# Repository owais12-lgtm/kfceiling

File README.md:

# kfceiling

# About
This is a macropad that has 8 programmable kets with a oled display and encoder! 

# Images

" height="626" alt="image" src="https://github.com/user-attachments/assets/a1786a0a-3907-4cc6-ba57-133aeb5b290b" />

# BOM

| Name | Purpose | Quantity | Total Cost (USD) | Link | Distributor |
|---|---|---|---|---|---|
| pcb | pcb | 1 | $0.00 | [robu.in](https://robu.in/product/online-pcb-manufacturing-service/) | robu |
| nice nano | mcu | 1 | $9.00 | [robu.in](https://robu.in/product/promicro-nrf52840-development-board/) | robu |
| shipping misc | its shipping | 1 | $5.00 | [robu.in](https://robu.in) | NA |
| oled | oled | 1 | $3.00 | [robu.in](https://robu.in/product/0-91-inch-128x32-i2c-iic-serial-oled-lcd-display-modulewith-gnd-vcc-white/) | robu |
| flux | flux | 1 | $1.70 | [probots.co.in](https://probots.co.in/tmyloku-nc-559-asm-soldering-flux-paste-10cc-syringe.html) | probot |
| Rotary Encoder EC11 | spiny thingy | 1 | $1.00 | [probots.co.in](https://probots.co.in/20-position-360-degree-rotary-encoder-ec11-w-push-button.html) | probots |
| solder | soldering | 2 | $5.52 | [robu.in](https://robu.in/product/solder-wire-0-5mm-50g-b-type-35-tin-content/) | robu |
| PTA2043-2015CPB103 | slider | 1 | $1.00 | [robu.in](https://robu.in/product/pta2043-2015cpb103-slide-potentiometers/) | robu |
| diode | ..its a diode | 200 | $3.00 | [robu.in](https://robu.in/product/1n4148-1w-zener-diode-pack-of-50/) | robu |
| switches | switches | 1 | $4.00 | [stackskb.com](https://stackskb.com/store/hmx-canglan-v3-pack-of-10/) | stackskb |

# CAD links
https://www.tinkercad.com/things/2FchFKunDui-swanky-bigery

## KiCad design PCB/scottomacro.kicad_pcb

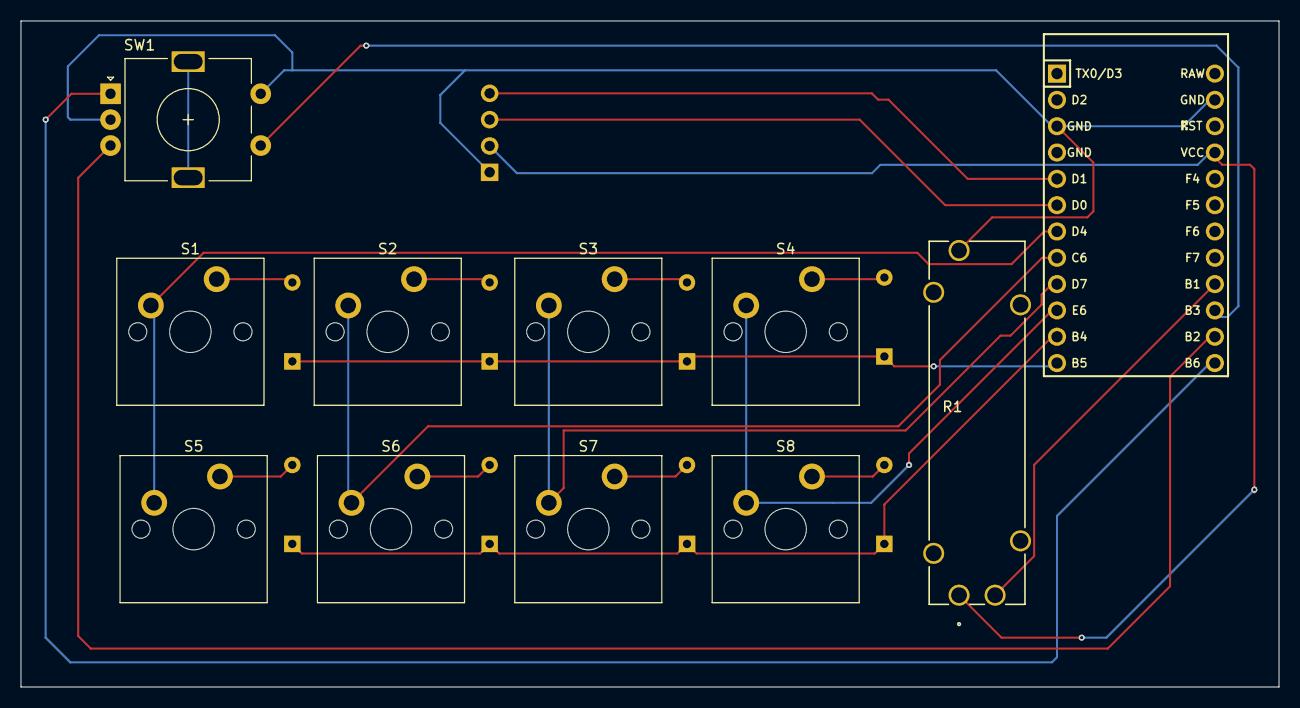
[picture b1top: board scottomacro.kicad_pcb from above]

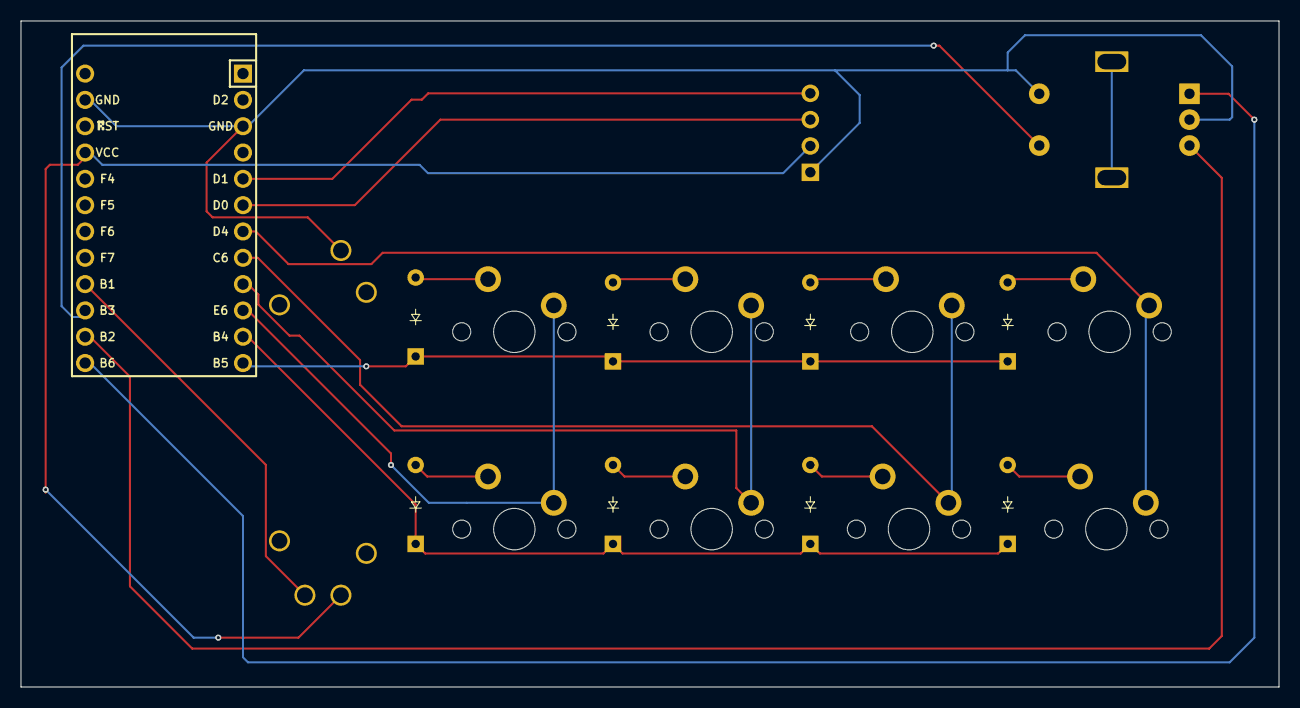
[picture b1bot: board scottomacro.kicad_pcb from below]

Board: 2 copper layers, 121.4 x 64.3 mm, 20 parts (8 on the bottom side), 22 nets.

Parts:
D1, D2, D3, D4, D5, D6, D7, D8: Diode_DO-35
J1: OLED_128x32
R1: PTA2043-2015DPB103; POT_PTA2043
S1, S2, S3, S4, S5, S6, S7, S8: MX_PCB_1.00u
SW1: RotaryEncoder_Switch_MP; RotaryEncoder_Alps_EC11E-Switch_Vertical_H20mm
U1: Arduino_Pro_Micro

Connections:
A: SW1.A, U1.13 (10/PB6)
B: SW1.B, U1.14 (16/PB2)
Column 0: S1.1, S5.1, U1.7 (4/PD4)
Column 1: S2.1, S6.1, U1.8 (5/PC6)
Column 2: S3.1, S7.1, U1.9 (6/PD7)
Column 3: S4.1, S8.1, U1.10 (7/PE6)
GND: J1.1 (GND), R1.3, SW1.C, SW1.S2, U1.3 (GND), U1.23 (GND)
LP 2: R1.2, U1.16 (15/PB1)
unnamed: D1.2 (A), S1.2
unnamed: D2.2 (A), S2.2
unnamed: D3.2 (A), S3.2
unnamed: D4.2 (A), S4.2
unnamed: D5.2 (A), S5.2
unnamed: D6.2 (A), S6.2
unnamed: D7.2 (A), S7.2
unnamed: D8.2 (A), S8.2
Row 0: D1.1 (K), D2.1 (K), D3.1 (K), D4.1 (K), U1.12 (9/PB5)
Row 1: D5.1 (K), D6.1 (K), D7.1 (K), D8.1 (K), U1.11 (8/PB4)
S1: SW1.S1, U1.15 (14/PB3)
SCL: J1.3 (SCL), U1.6 (3/PD0)
SDA: J1.4 (SDA), U1.5 (2/PD1)
VCC: J1.2 (VCC), R1.1, U1.21 (VCC)
